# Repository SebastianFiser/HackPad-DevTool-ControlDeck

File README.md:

# HackPad-DevTool-ControlDeck

Core idea ?
Physical, context-awaree control console for Linux workflows.

**Goals**
Faster workflow,
system mods,
kontext logic,
physical ergonomy.

Hardware:
XIAO RP2040,
16x MX,
2x encoder,
OLED,
RGB,

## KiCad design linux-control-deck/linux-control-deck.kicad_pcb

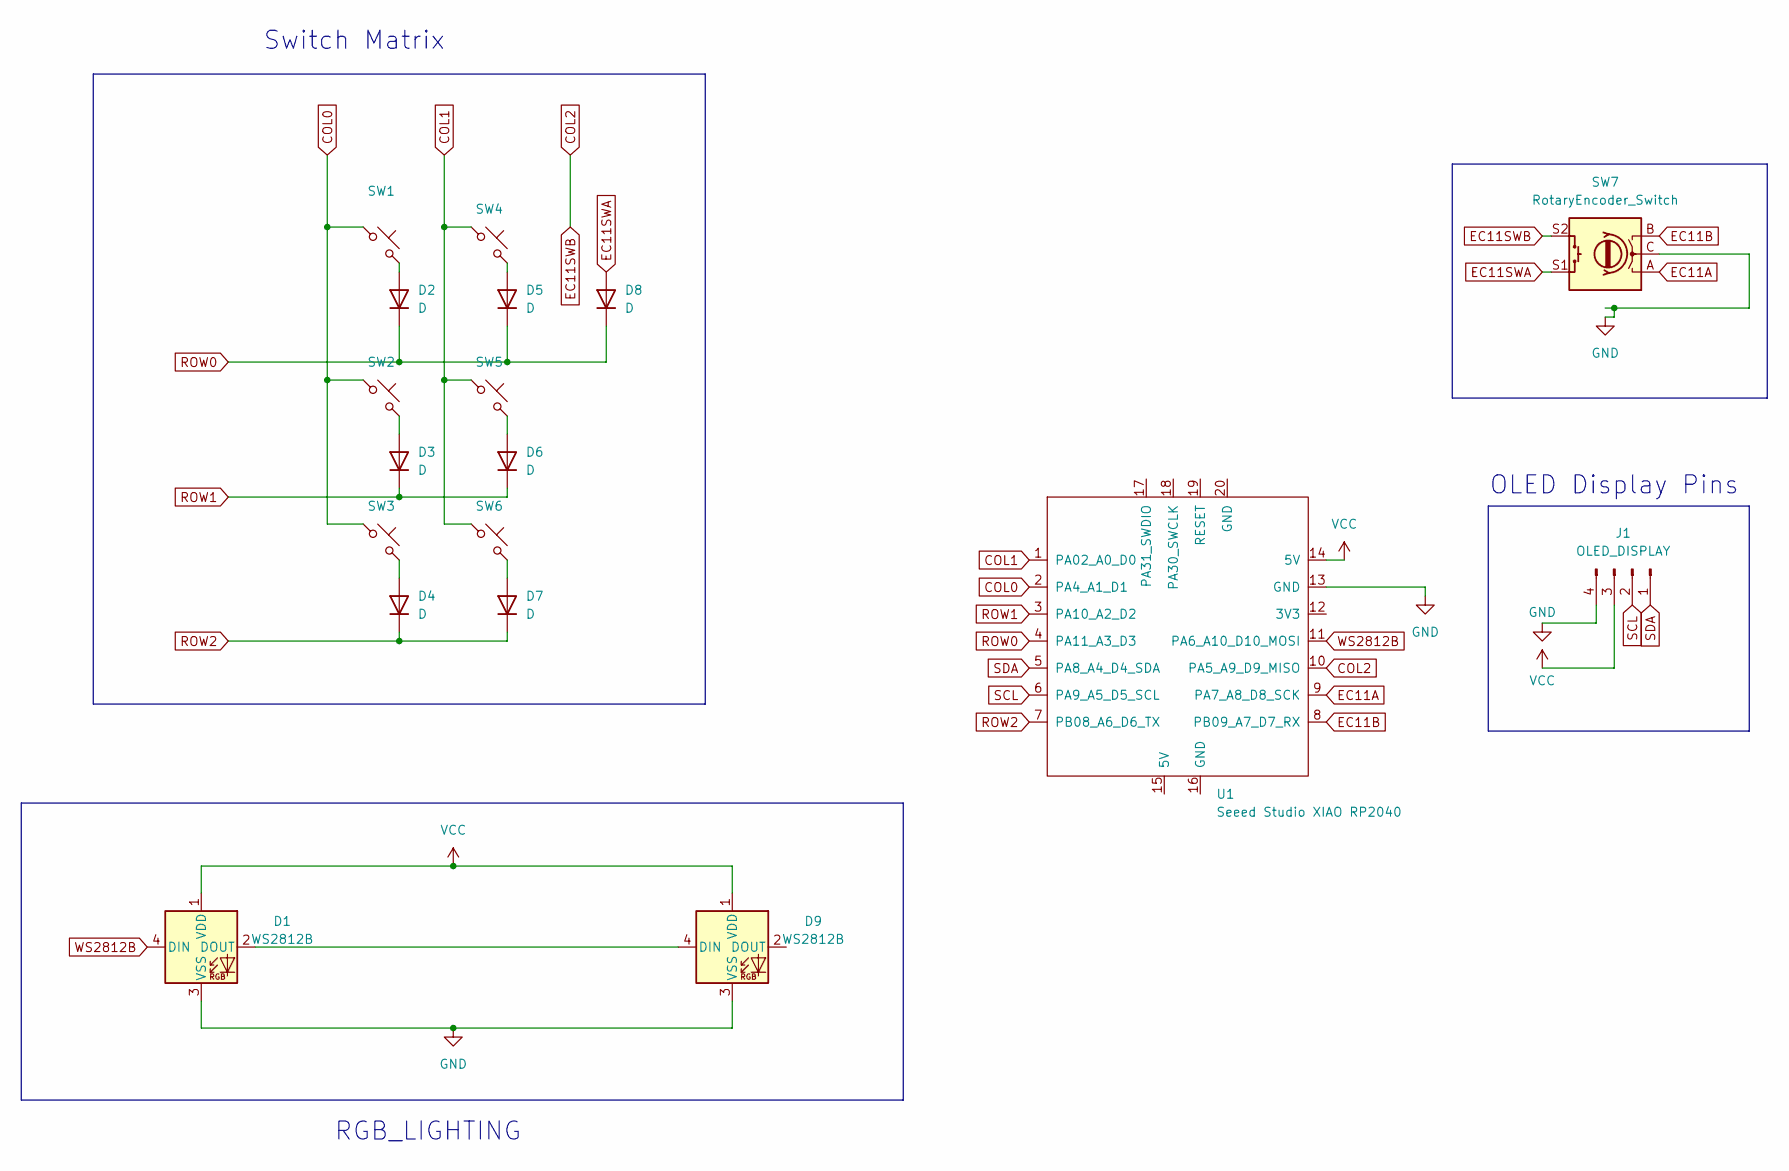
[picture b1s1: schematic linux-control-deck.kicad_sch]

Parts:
D1, D9: WS2812B; LED_WS2812B_PLCC4_5.0x5.0mm_P3.2mm
D2, D3, D4, D5, D6, D7, D8: D; D_DO-35_SOD27_P7.62mm_Horizontal
J1: OLED_DISPLAY; PinHeader_1x04_P2.54mm_Vertical
SW1, SW2, SW3, SW4, SW5, SW6: SW_Push_45deg; MX-Solderable-1U
SW7: RotaryEncoder_Switch; RotaryEncoder_Alps_EC11E-Switch_Vertical_H20mm
U1: Seeed Studio XIAO RP2040; XIAO-Generic-Hybrid-14P-2.54-21X17.8MM

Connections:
COL0: SW1.1, SW2.1, SW3.1, U1.2 (PA4_A1_D1)
COL1: SW4.1, SW5.1, SW6.1, U1.1 (PA02_A0_D0)
COL2: SW7.S2, U1.10 (PA5_A9_D9_MISO)
EC11A: SW7.A, U1.9 (PA7_A8_D8_SCK)
EC11B: SW7.B, U1.8 (PB09_A7_D7_RX)
EC11SWA: D8.2 (A), SW7.S1
GND: D1.3 (VSS), D9.3 (VSS), J1.4, SW7.C, U1.13 (GND)
unnamed: D1.2 (DOUT), D9.4 (DIN)
unnamed: D2.2 (A), SW1.2
unnamed: D3.2 (A), SW2.2
unnamed: D4.2 (A), SW3.2
unnamed: D5.2 (A), SW4.2
unnamed: D6.2 (A), SW5.2
unnamed: D7.2 (A), SW6.2
ROW0: D2.1 (K), D5.1 (K), D8.1 (K), U1.4 (PA11_A3_D3)
ROW1: D3.1 (K), D6.1 (K), U1.3 (PA10_A2_D2)
ROW2: D4.1 (K), D7.1 (K), U1.7 (PB08_A6_D6_TX)
SCL: J1.2, U1.6 (PA9_A5_D5_SCL)
SDA: J1.1, U1.5 (PA8_A4_D4_SDA)
VCC: D1.1 (VDD), D9.1 (VDD), J1.3, U1.14 (5V)
WS2812B: D1.4 (DIN), U1.11 (PA6_A10_D10_MOSI)

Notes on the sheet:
OLED Display Pins
RGB_LIGHTING
Switch Matrix

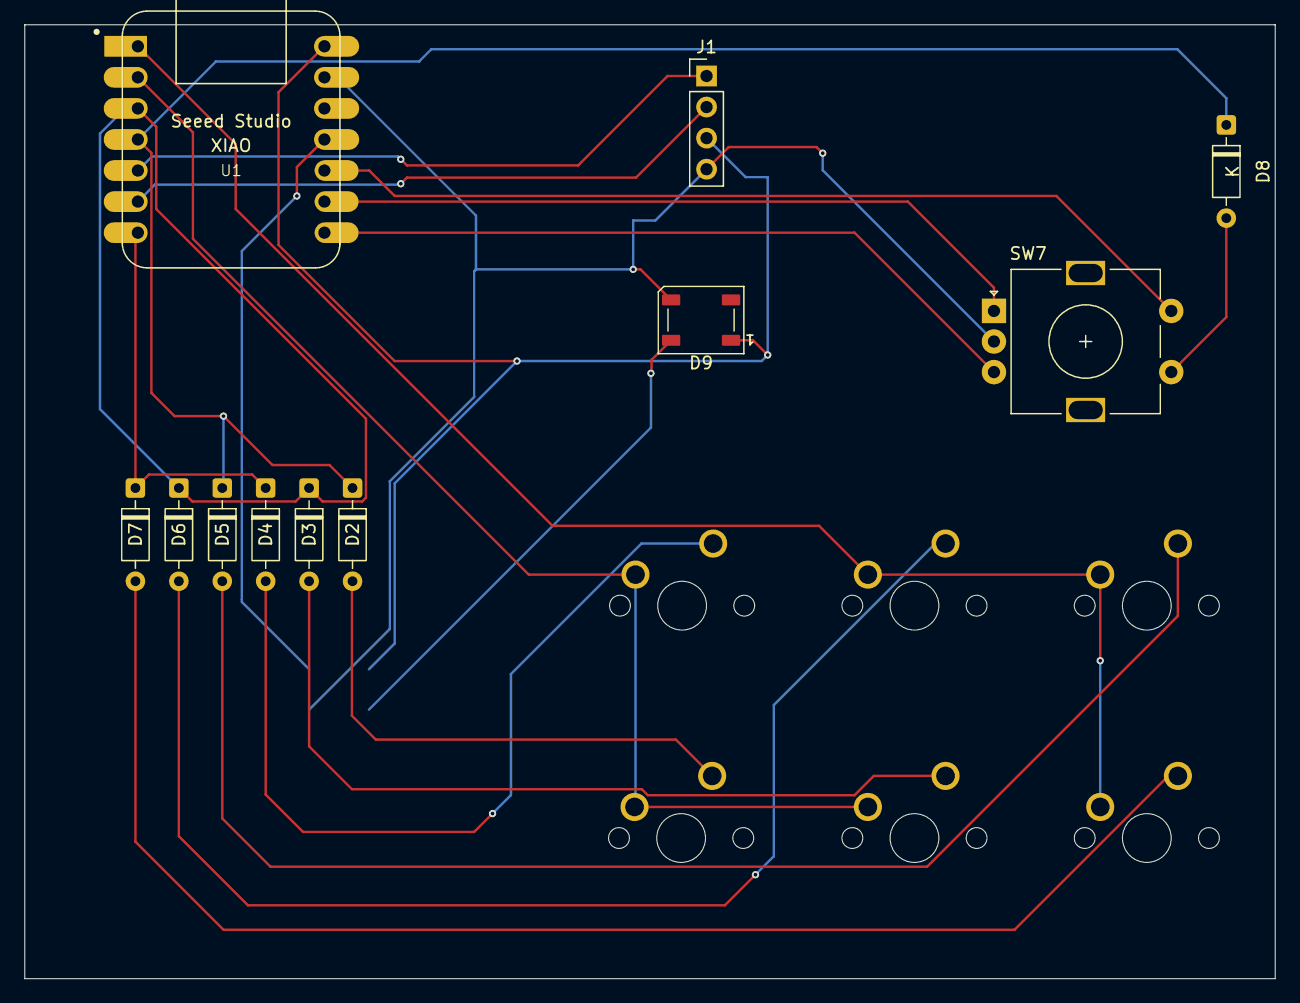
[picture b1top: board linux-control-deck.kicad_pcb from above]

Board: 2 copper layers, 102.2 x 78.0 mm, 18 parts (1 on the bottom side), 21 nets.

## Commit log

2026-02-19 Update README with project overview and specifications
    Added project description, goals, and hardware details.
2026-02-19 Fix punctuation and formatting in README.md
    Corrected punctuation and formatting in README.
2026-02-19 repo work
2026-02-19 updated docs
2026-02-22 PCB layout and wiring complete
2026-02-25 PCB work finished, starting firmware work
2026-02-25 Cleanup work
2026-02-25 strated work on keypad
